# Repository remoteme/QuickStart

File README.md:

QuickStart - DO NOT USE IT FOR MOST OF YOU ITS JUST USELESS

I'm using this for project QuickStart at the app.remoteme.org welcome Page.
It doesnt containt any usefull quickstart projects. But If You want to create your worn quick start project You can see how its done fork it then merge it into base your changes and will be available for everyone ;)

Photos belongs or to RemoteMe, or for parts to the shop in certain product link. Do not copy.

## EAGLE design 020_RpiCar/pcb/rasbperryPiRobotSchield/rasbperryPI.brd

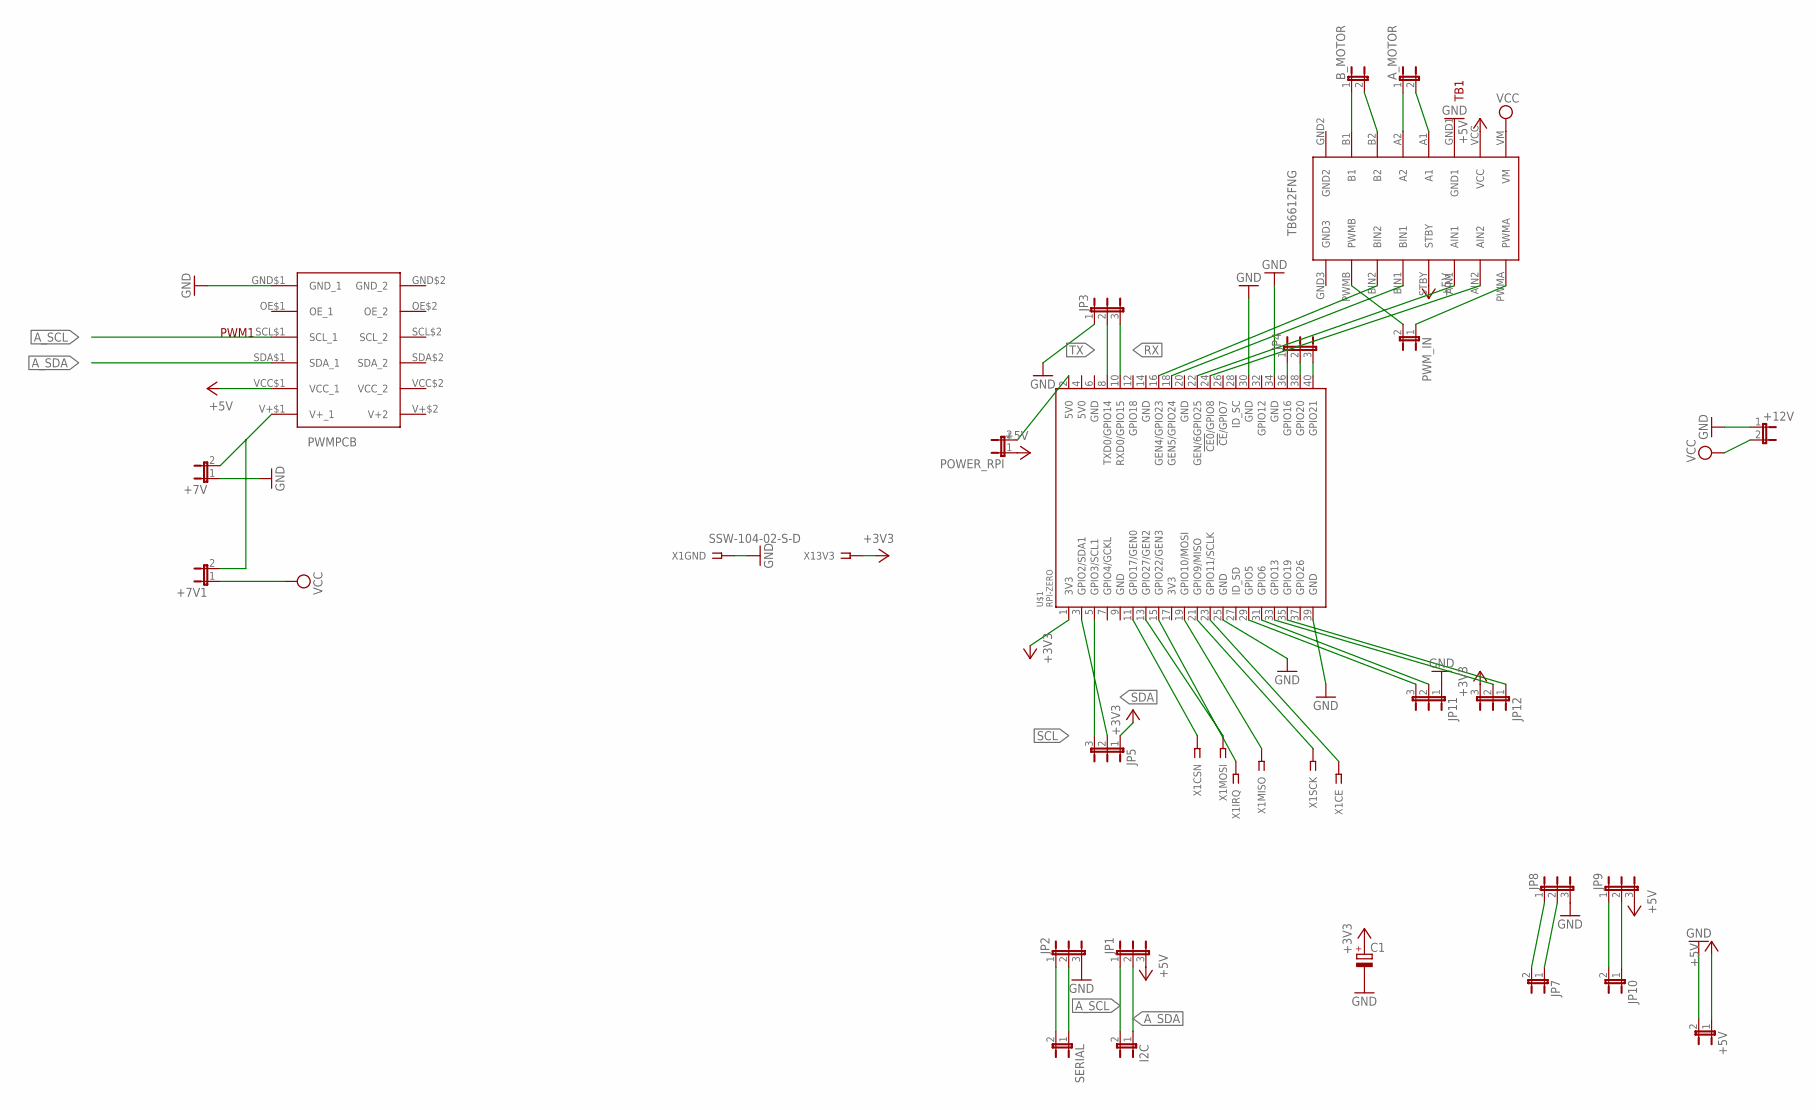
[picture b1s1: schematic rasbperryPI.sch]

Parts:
+5V, +7V, +7V1, +12V: JP1E; JP1
A_MOTOR: JP1E; JP1
B_MOTOR: JP1E; JP1
C1: CPOL-EUE2,5-6E; E2,5-6E
I2C: JP1E; JP1
JP1, JP2, JP3, JP4, JP5, JP8, JP9, JP11, JP12: JP2E; JP2
JP7, JP10: JP1E; JP1
POWER_RPI: JP1E; JP1
PWM1: PWMPCB; PWM
PWM_IN: JP1E; JP1
SERIAL: JP1E; JP1
TB1: TB6612FNG
U$1: RPI-ZERO; RASP_PI_ZERO_BOARD_FULL
X1: SSW-104-02-S-D

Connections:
5V0@1: POWER_RPI.2, U$1.2 (5V0)
+3V3: C1.+, JP5.1, JP12.3, U$1.1 (3V3), X1.2
+5V: +5V.1, JP1.3, JP9.3, POWER_RPI.1, PWM1.VCC$1 (VCC_1), TB1.STBY, TB1.VCC
A_SCL: I2C.2, JP1.1, PWM1.SCL$1 (SCL_1)
A_SDA: I2C.1, JP1.2, PWM1.SDA$1 (SDA_1)
GND: +5V.2, +7V.1, +12V.1, C1.-, JP2.3, JP3.1, JP8.3, JP11.1, PWM1.GND$1 (GND_1), TB1.GND1, U$1.25 (GND), U$1.30 (GND), U$1.34 (GND), U$1.39 (GND), X1.1
unnamed: +7V.2, +7V1.2, PWM1.V+$1 (V+_1)
unnamed: JP4.1, U$1.36 (GPIO16)
unnamed: U$1.11 (GPIO17/GEN0), X1.4
unnamed: U$1.13 (GPIO27/GEN2), X1.6
unnamed: U$1.15 (GPIO22/GEN3), X1.8
unnamed: U$1.19 (GPIO10/MOSI), X1.7
unnamed: U$1.21 (GPIO9/MISO), X1.5
unnamed: U$1.23 (GPIO11/SCLK), X1.3
unnamed: JP11.3, U$1.29 (GPIO5)
unnamed: JP11.2, U$1.31 (GPIO6)
unnamed: PWM_IN.1, TB1.PWMA
unnamed: PWM_IN.2, TB1.PWMB
unnamed: JP12.2, U$1.33 (GPIO13)
unnamed: JP12.1, U$1.35 (GPIO19)
unnamed: B_MOTOR.1, TB1.B1
unnamed: B_MOTOR.2, TB1.B2
unnamed: A_MOTOR.1, TB1.A2
unnamed: A_MOTOR.2, TB1.A1
unnamed: JP2.1, SERIAL.2
unnamed: JP2.2, SERIAL.1
unnamed: TB1.BIN2, U$1.16 (GEN4/GPIO23)
unnamed: TB1.BIN1, U$1.18 (GEN5/GPIO24)
unnamed: TB1.AIN1, U$1.22 (GEN/6GPIO25)
unnamed: TB1.AIN2, U$1.24 (!CE0!/GPIO8)
unnamed: JP7.2, JP8.1
unnamed: JP7.1, JP8.2
unnamed: JP9.1, JP10.2
unnamed: JP9.2, JP10.1
unnamed: JP4.2, U$1.38 (GPIO20)
unnamed: JP4.3, U$1.40 (GPIO21)
RX: JP3.3, U$1.10 (RXD0/GPIO15)
SCL: JP5.3, U$1.5 (GPIO3/SCL1)
SDA: JP5.2, U$1.3 (GPIO2/SDA1)
TX: JP3.2, U$1.8 (TXD0/GPIO14)
VCC: +7V1.1, +12V.2, TB1.VM

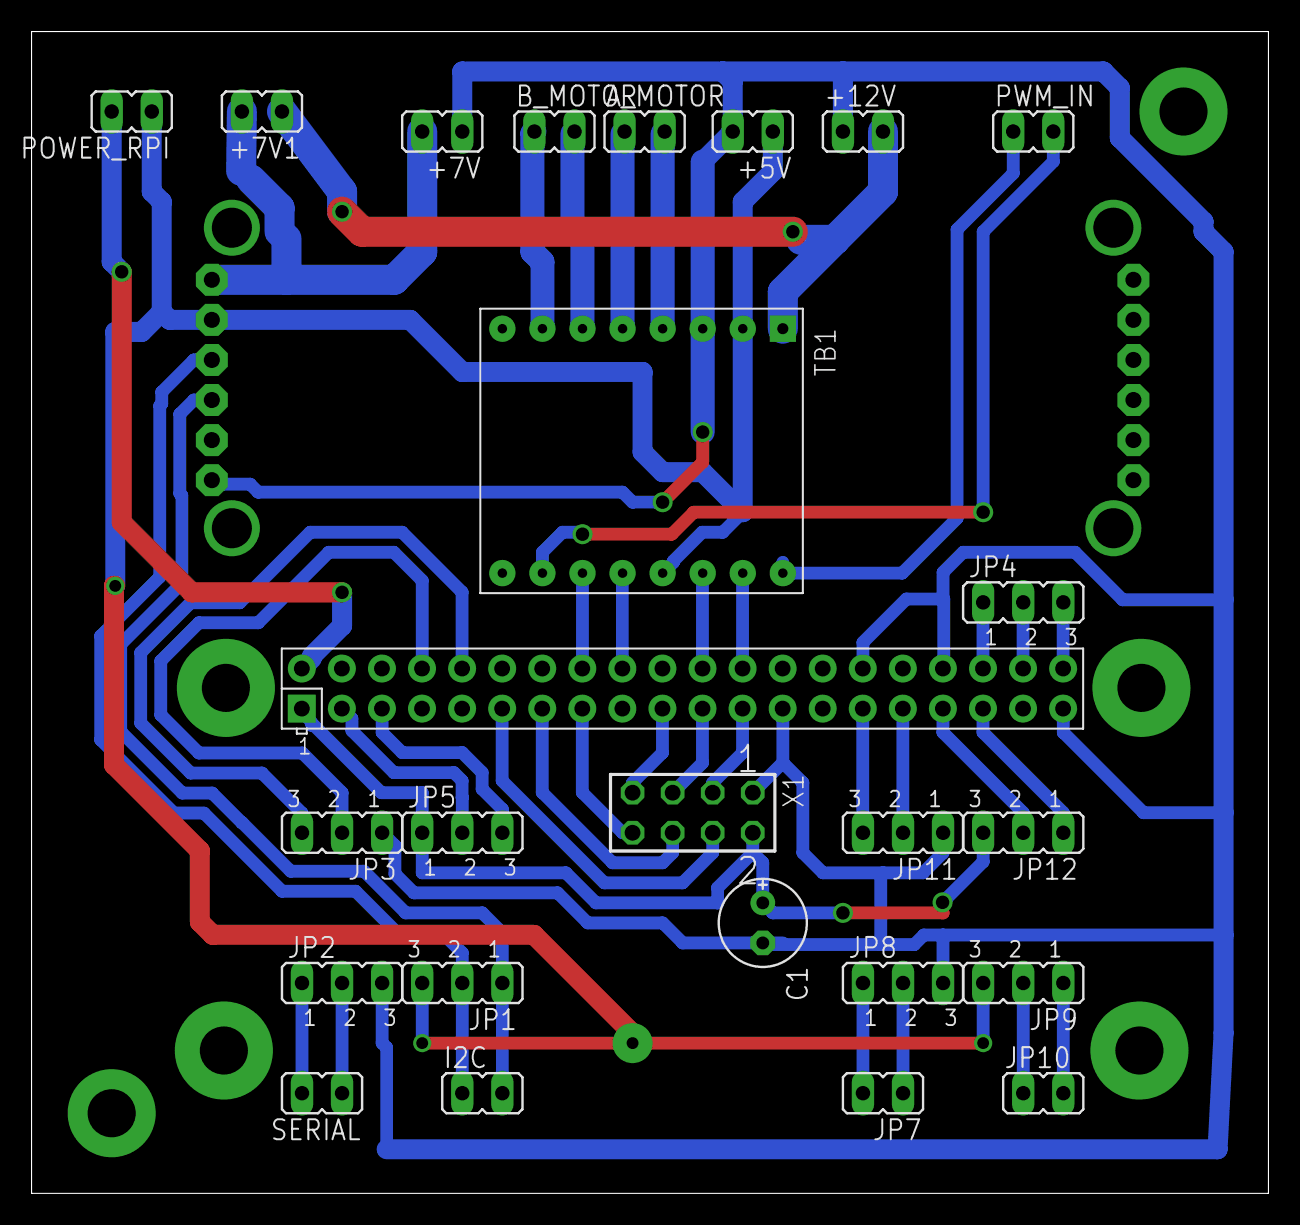
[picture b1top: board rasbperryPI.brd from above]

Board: 2 copper layers, 78.4 x 73.6 mm, 26 parts (1 on the bottom side), 41 nets.

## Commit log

2019-02-13 initial readme
2019-02-13 next quickstart Page
2019-02-17 mobile suppor
2019-02-20 before generate DTO
2019-02-24 next quickstart wizard
2019-03-04 some initial examples
2019-03-04 remove files
2019-03-04 add to ignoer
2019-03-05 next quickstart
2019-03-05 add placeholders
2019-03-06 rpi led blinking + some bugs and utils
2019-03-07 next Rpi device quickstart + repairing some stuff
2019-03-07 small mistakes
2019-03-09 add rpi car
2019-03-10 next repairingwebrtc
2019-03-10 increase timeout for gyroscope
2019-03-11 some mistakes
2019-03-12 botland as partner
2019-03-12 add parts and updates
2019-03-16 next personal project eiditing
2019-03-16 more features and project renaming
2019-03-17 better icons better navigations
2019-03-17 added photos
2019-03-17 next
2019-03-18 update quickstart
2019-03-18 Rpi car quickstart project next
2019-03-18 add misisng files
2019-03-18 add ph
2019-03-18 udpate variable cahgnes
2019-03-18 added calibrarion device
2019-03-18 next better quick start prjectsc
2019-03-18 next tutorial
2019-03-22 next rpi tutorial
2019-03-22 add link to the tutorial
2019-03-24 update project files
2019-03-24 hppts
2019-03-25 next tutorials and stuff
2019-03-26 next tutrial + cosmetics
2019-03-26 added avatar
2019-03-27 isntallation for android
2019-03-28 next android app and move scripts
2019-03-30 device connection status
2019-03-30 next installation etc
2019-03-31 update connections
2019-03-31 update description
2019-03-31 add missing files
2019-04-13 new quick start project + cosmetics
2019-04-13 change order of project
2019-04-13 make project hidden
2019-04-14 add comments
2019-04-14 repair error
2019-04-14 update logger and quickstart project
2019-05-08 added imports
2019-05-14 better look + configration in one palce + better file replacement if enw
2019-05-14 next project
2019-05-18 add sync messages example
2019-05-19 initial of camera quick project
2019-05-20 more bullet proof schedulers
2019-05-20 repair mistakes
2019-05-21 add for quickstart
2019-05-22 make not hidden
2019-06-06 next quick start project
2019-06-08 update [arts
2019-06-08 update parts
2019-06-12 update style back
2019-06-17 add plly fill
2019-06-23 make eather public
2019-06-25 update required libraries
2019-06-25 add tour
2019-07-22 next and update files
2019-07-24 next integration with webpagetoken
2019-07-29 nextrental support + some little bugs
2019-09-14 youtube project + some bugs
2019-09-16 repair quick start project youtube
2019-09-16 next youtube project
2019-09-16 unhidden tyoutube project
2019-09-16 repair youtube project
2019-09-21 start adding new project
2019-09-22 update project
2019-09-22 repair quick projects
2019-09-25 add quick start project esp32cam
2019-10-03 update gaelery component
2020-02-23 faster
2020-02-29 next version
2020-03-02 docuemntation update and cleaning code
2020-04-26 repair bugs
2021-09-25 repair json
